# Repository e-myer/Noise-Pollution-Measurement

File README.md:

# Noise-Pollution-Measurement
This is the GitHub Repository for the Noise Pollution Measurement device by "Awaaj Koto?" \
Visit www.noisepollution.fablabdhaka.com to know more about the project

The current hardware and software versions we are using is ["Vervet"](https://github.com/AmirSamir92/Noise-Pollution-Measurement/tree/master/Hardware/Vervet) \
The current casing version we are using is ["Flat"](https://github.com/AmirSamir92/Noise-Pollution-Measurement/tree/master/Casing/Print_Ready/Flat)

## List of components required

## Electronics:

- **Battery Li-ion Rechargeable 18650** \
Link: https://www.electronics.com.bd/batteries/batteryli-ion-rechargeable-(small-sun)-18650-3.7v-2200mah%20-electronics-parts-sensors-robotics-bangladesh

- **Battery Case** \
Link: https://www.electronics.com.bd/batteries/battery-box-case-18650-a-single-battery-charging-cradle-with-thick-lines

- **Battery Charger Circuit** \
Link: https://www.electronics.com.bd/board/lithium-mini-3.7v-battery-protection-board-tp4056)

- **Arduino Nano** \
Link: https://www.electronics.com.bd/arduino-nano-v3.0-electronics-parts-microcontrollers-robotics-bangladesh?search=arduino%20nano)

- **SIM800L GSM Module** \
Link: https://www.electronics.com.bd/sim-800l-parts-IC-module-sensor-arduino-transistor-resistor-capacitor-robotics-project-electronics-bangladesh%20(jobayer%20ahmed's%20conflicted%20copy%202017-01-29)?search=sim800

- **6V 1.1W Solar** \
Link: http://bdspeedytech.com/index.php?route=product/product&product_id=2504&search=solar

- **Grove - Loudness Sensor** \
Link: https://www.techshopbd.com/product-categories/sound/1261/grove-loudness-sensor-techshop-bangladesh

## Casing:

- [**Casing Bottom**](https://github.com/AmirSamir92/Noise-Pollution-Measurement/blob/master/Casing/Print_Ready/Flat/3d%20model%20bottom.stl)
- [**Casing Shelf**](https://github.com/AmirSamir92/Noise-Pollution-Measurement/blob/master/Casing/Print_Ready/Flat/3d%20model%20top.stl)
- **Casing Cover** 

**The parts of the casing can be 3D printed at home or by one of these services:**

- EMK MakerLab at the [EMK Center](https://www.emkcenter.org/)

## Contributors:

- Md Khairul Alam Taifur
- Tauseef Anwaar
- Amir Samir
- Jarir Tushar
- Zaimul Nihal
- Mobasheer Meead
- Tahreem Shah
- Sharif Khan
- Mahmudul Islam Chowdhury
- Asifur Rahman
- Hasib Zunair
- Tanzil Shahria
- Aimon Rahman Snigdha
- Fahmida Afrin
- Farzana Yesmin
- Tabinda Rahman Chowdhury
- Oisin Maniya Hiya Mahbub
- Najmus Bappy

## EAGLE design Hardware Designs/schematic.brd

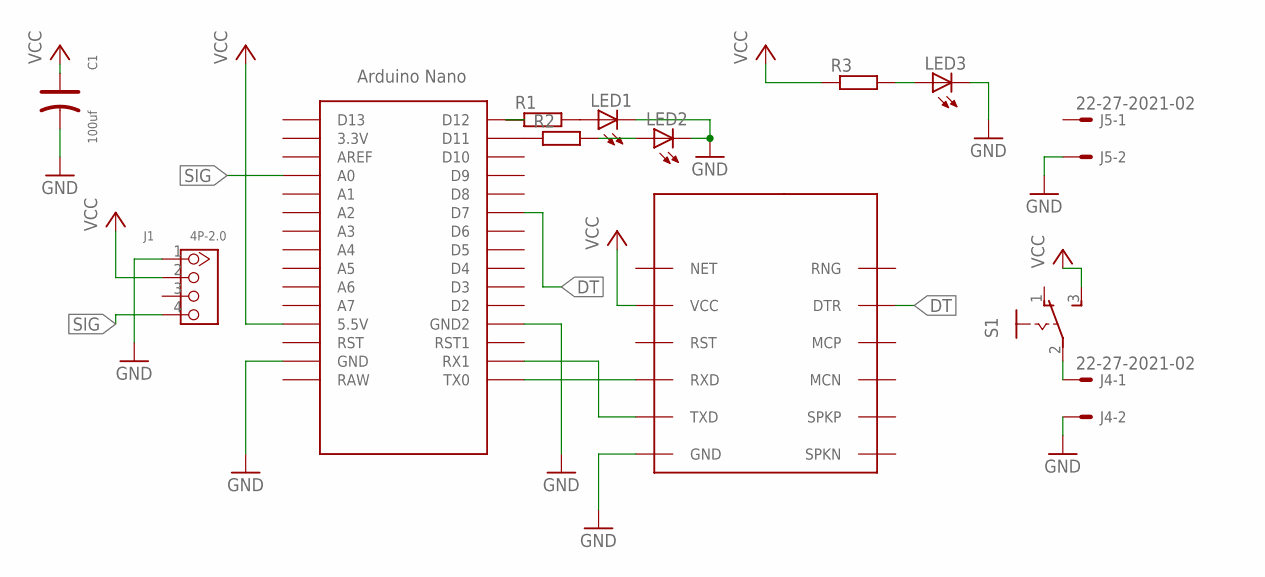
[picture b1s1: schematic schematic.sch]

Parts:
C1: 100uf; PC-D5.3MM
J1: 4P-2.0; HW4-2.0
J4, J5: 22-27-2021-02; 6410-02
LED1, LED2, LED3: LED5MM
R1, R2, R3: R-EU_0204/7; 0204/7
S1: M251
U$1: NANO
U$2: SIM800L; SIM-CORE

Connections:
DT: U$1.D7, U$2.DTR
GND: C1.-, J1.1, J4.2, J5.2, LED1.K (C), LED2.K (C), LED3.K (C), U$1.GND, U$1.GND1 (GND2), U$2.GND
unnamed: U$1.TX0, U$2.RXD
unnamed: U$1.RX1, U$2.TXD
unnamed: R1.1, U$1.D12
unnamed: R2.1, U$1.D11
unnamed: LED1.A, R1.2
unnamed: LED2.A, R2.2
unnamed: LED3.A, R3.2
unnamed: J4.1, S1.2
SIG: J1.4, U$1.A0
VCC: C1.+, J1.2, R3.1, S1.3 (S), U$1.5V (5.5V), U$2.VCC

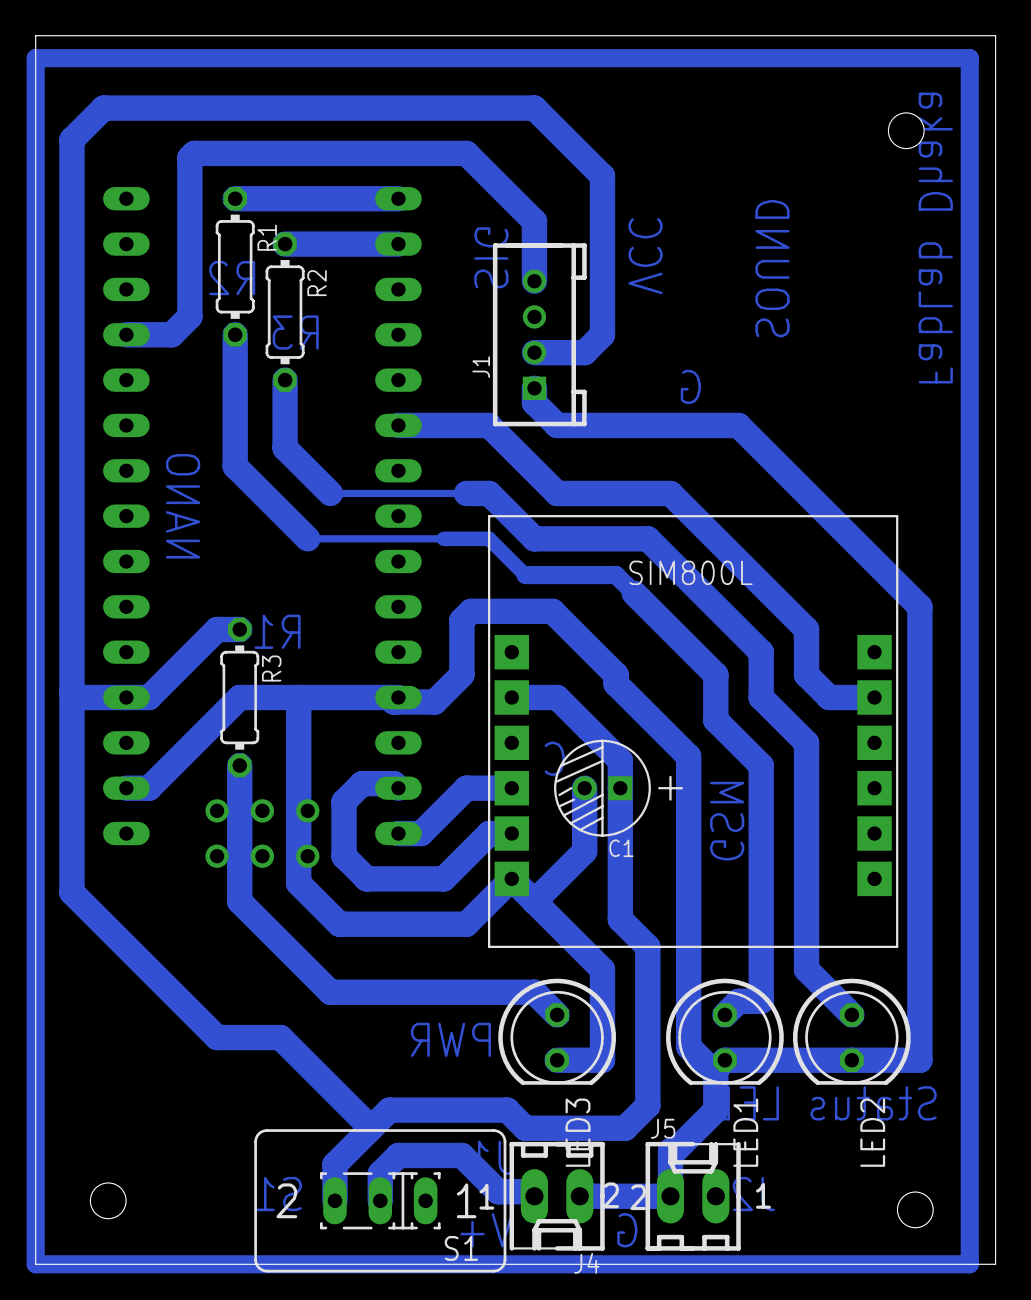
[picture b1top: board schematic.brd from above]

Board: 2 copper layers, 53.8 x 68.8 mm, 13 parts (0 on the bottom side), 12 nets.

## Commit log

2018-06-10 Create dummy file
2018-07-04 Create Code 2
2018-07-04 Rename Code/noise.ino to Code 1
2018-07-04 Rename Code 1 to Code/Code 1
2018-07-22 Rename Code 1 to Lemur
2018-07-22 Rename Code 2 to Vervet
2018-07-22 Rename Code v0.1 to Marmoset
2018-07-22 Rename Hardware Designs/schematic.sch to Hardware Designs/Vervet/schematic.sch
2018-11-23 Update Dummy file
2018-11-24 Rename Hardware Designs/Vervet/Dummy file to Hardware/Vervet/Dummy file
